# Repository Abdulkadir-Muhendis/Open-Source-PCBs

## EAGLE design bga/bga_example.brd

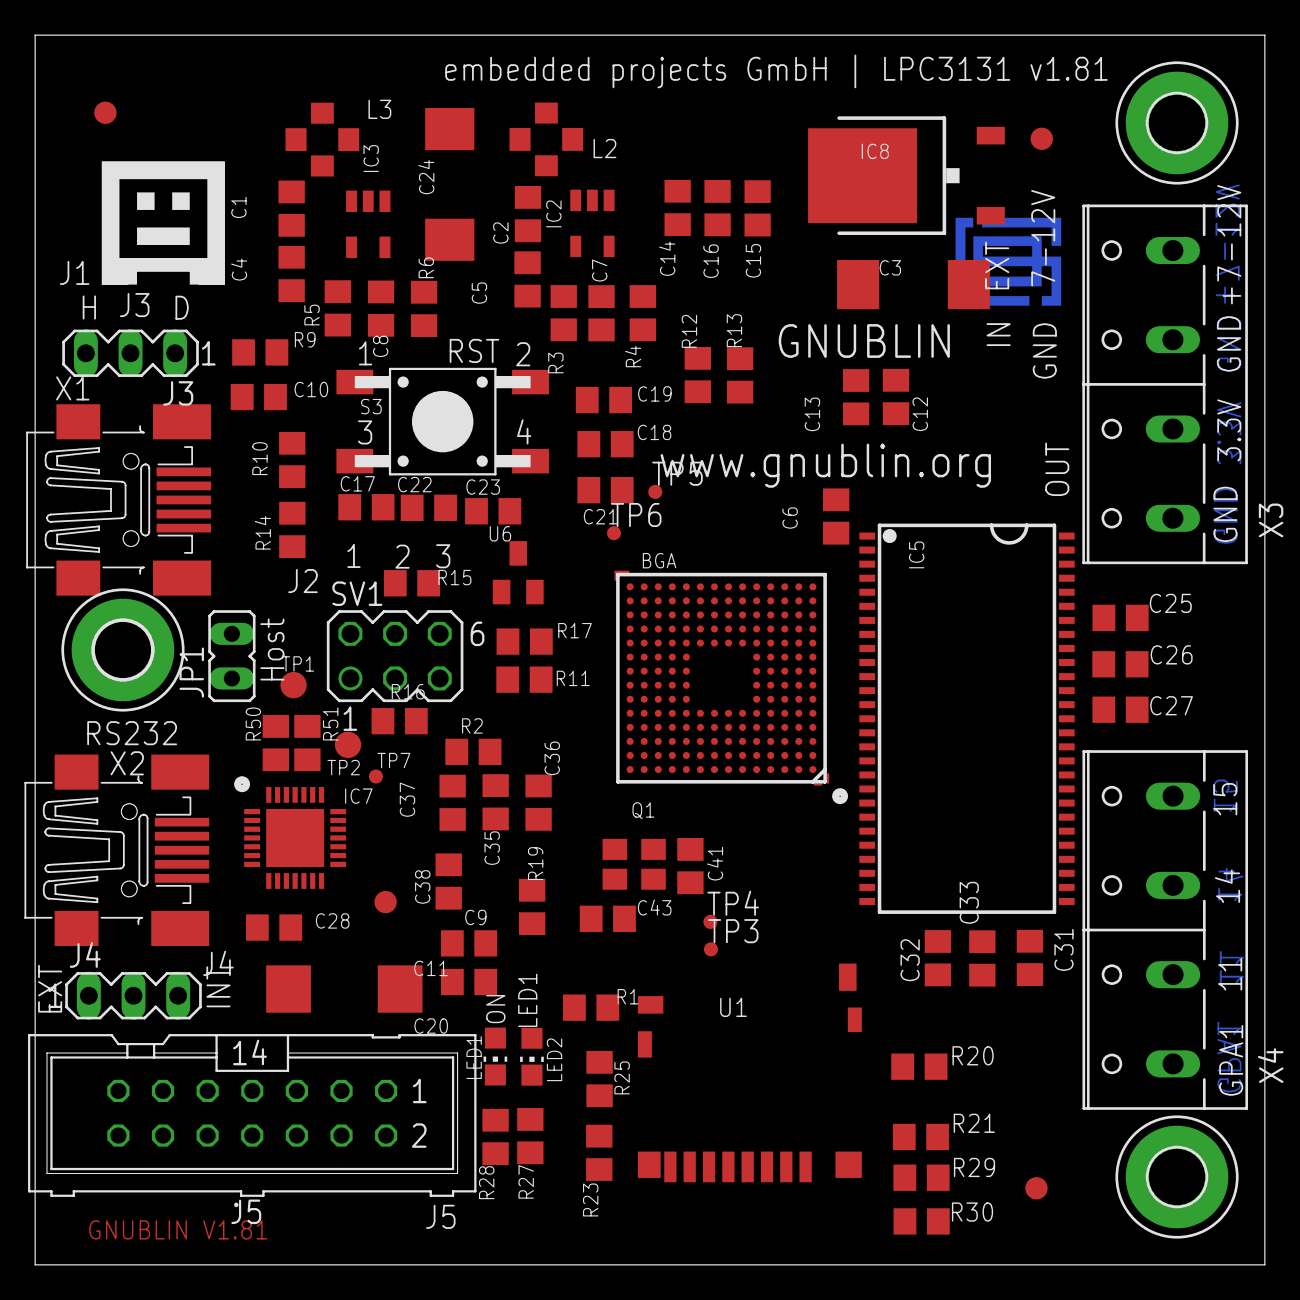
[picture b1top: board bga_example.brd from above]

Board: 4 copper layers, 70.0 x 70.0 mm, 102 parts (1 on the bottom side), 101 nets.

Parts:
BGA: LPC313XFET180; TFBGA180
C1, C2, C11, C13, C14, C21, C23, C27, C32, C37: 10uF; C0805
C3, C24: 10uF; SMC_D
C4, C5: 4.7uF; C0805
C6, C9, C10, C16, C18, C22, C26, C33, C35, C38: 100nF; C0805
C7, C8, C41, C43: 22pF; C0805
C12, C15, C17, C19, C25, C31, C36: 3.3nF; C0805
C20: 10uF; D/7343-31R
C28: 2.2uF; C0805
FID1, FID2, FID3, FID4: PASSERMARKEN_FIDUCIAL
H1, H4: MOUNT-PAD-ROUND3.2; 3,2-PAD
H2: MOUNT-PAD-ROUND3.3; 3,3-PAD
IC2, IC3: AS1324; TSOT23
IC5: A43E26161TSOPII; TSOPII
IC7: CP21021; MLP28
IC8: MC78M05ABDT; DPACK_3
J3, J4: MA03-1
J5: ML14
JP1: JP1
L2, L3: 4u7; PSU3014
LED1: GRUEN; CHIP-LED0805
LED2: ROT; CHIP-LED0805
Q1: SX-32 12.000 MHz; SX-32
R1, R2, R9, R12, R15, R16, R17, R20, R21, R23, R25, R29, R30: 10K; R0805
R3, R4, R5: 301K; R0805
R6: 66K5; R0805
R10, R14: 1M; R0805
R11: 12K 1%; R0805
R13: DNP; R0805
R19: 22R; R0805
R27, R28: 270R; R0805
R50, R51: 0R; R0805
S3: TASTER-9314_SMD
SV1: MA03-2
TP1, TP2: TPTP15R; TP15R
TP3, TP4: PTR1TP08R; TP08R
TP5, TP6, TP7: TPTP08R; TP08R
U1: DM3D-SF
U6: APX803; SOT23
U$3: GNUBLINLOGOSIEB; GNUSIEBDRUCK
U$4: EPLOGO; EPLOGOKUPFER
X1, X2: MINI-USB-32005-201; 32005-201
X3, X4: W237-4P

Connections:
5V: C4.1, C5.1, C20.+, C24.+, C28.1, IC2.1, IC2.4, IC3.1, IC3.4, IC7.7, IC7.8, J3.3, J4.2
+1V2: BGA.A9, BGA.C6, BGA.C9, BGA.C12, BGA.D11, BGA.E10, BGA.H3, BGA.L1, BGA.L7, BGA.L12, C2.2, C7.1, C18.2, C19.2, C21.2, C35.2, C36.2, C37.2, C38.2, L2.2, R3.2
+3V3: BGA.B2, BGA.C13, BGA.D5, BGA.D7, BGA.E5, BGA.E8, BGA.F5, BGA.G5, BGA.G12, BGA.H5, BGA.K11, BGA.L4, BGA.L10, BGA.M2, BGA.M5, BGA.M7, BGA.M9, BGA.P1, C1.2, C6.2, C8.1, C12.2, C13.2, C14.2, C15.2, C16.2, C17.2, C22.2, C23.2, C25.2, C26.2, C27.2, C31.2, C32.2, C33.2, IC5.1, IC5.3, IC5.9, IC5.14, IC5.27, IC5.43, IC5.49, J5.13, L3.2, LED1.A, R1.2, R2.1, R5.2, R12.2, R17.2, R19.1, R20.1, R21.1, R23.1, R25.1, R29.1, R30.1, SV1.5, SV1.6, U1.4, U6.3, X3.2
+5V_USB: J4.3, X2.1
+7-12V: C3.+, IC8.1, X3.4
D+: IC7.4, X2.3
D-: IC7.5, X2.2
EXT_5V: IC8.3, J4.1
GND: BGA.A11, BGA.A12, BGA.B12, BGA.C3, BGA.C4, BGA.C7, BGA.D6, BGA.D8, BGA.D9, BGA.D12, BGA.E4, BGA.E9, BGA.F4, BGA.G4, BGA.G11, BGA.H4, BGA.K3, BGA.K4, BGA.L3, BGA.L6, BGA.L9, BGA.L11, BGA.L13, BGA.M3, BGA.M4, BGA.M6, BGA.M8, BGA.N1, C1.1, C2.1, C3.-, C4.2, C5.2, C6.1, C9.1, C10.1, C11.1, C12.1, C13.1, C14.1, C15.1, C16.1, C17.1, C18.1, C19.1, C20.-, C21.1, C22.1, C23.1, C24.-, C25.1, C26.1, C27.1, C28.2, C31.1, C32.1, C33.1, C35.1, C36.1, C37.1, C38.1, C41.1, C43.1, IC2.2, IC3.2, IC5.6, IC5.12, IC5.28, IC5.41, IC5.46, IC5.52, IC5.54, IC7.3, IC7.EXP, IC8.4, J5.14, JP1.1, R4.1, R6.1, R10.1, R11.1, R13.1, R14.1, R27.1, R28.1, S3.3, S3.4, SV1.1, SV1.2, U1.6, U1.SW_B, U6.1, X1.5, X2.5, X3.1, X3.3
GPA0: BGA.B14, J5.1
GPA1: BGA.A14, J5.2, X4.1
GPA3: BGA.C14, J5.3
GPIO0: BGA.K10, R15.1
GPIO2: BGA.L14, R16.2
GPIO11: BGA.H13, J5.12, X4.2
GPIO14: BGA.J14, J5.11, X4.3
GPIO15: BGA.J13, X4.4
I2C_SCL: BGA.E13, J5.5
I2C_SDA: BGA.E12, J5.6
LED1: BGA.B11, LED2.A
LPC_A0: BGA.B3, IC5.23
LPC_A1: BGA.A2, IC5.24
LPC_A2: BGA.N6, IC5.25
LPC_A3: BGA.P6, IC5.26
LPC_A4: BGA.N7, IC5.29
LPC_A5: BGA.P7, IC5.30
LPC_A6: BGA.K6, IC5.31
LPC_A7: BGA.P5, IC5.32
LPC_A8: BGA.N5, IC5.33
LPC_A9: BGA.L5, IC5.34
LPC_A10: BGA.K7, IC5.22
LPC_A11: BGA.N4, IC5.35
LPC_A12: BGA.K5, IC5.36
LPC_A13: BGA.P4, IC5.21
LPC_A14: BGA.P3, IC5.20
LPC_CAS: BGA.G1, IC5.17
LPC_CKE: BGA.L8, IC5.37
LPC_CLK: BGA.N8, IC5.38
LPC_CS: BGA.P8, IC5.19
LPC_D0: BGA.G2, IC5.2
LPC_D1: BGA.F2, IC5.4
LPC_D2: BGA.F1, IC5.5
LPC_D3: BGA.E1, IC5.7
LPC_D4: BGA.E2, IC5.8
LPC_D5: BGA.D1, IC5.10
LPC_D6: BGA.D2, IC5.11
LPC_D7: BGA.C1, IC5.13
LPC_D8: BGA.B1, IC5.42
LPC_D9: BGA.A3, IC5.44
LPC_D10: BGA.A1, IC5.45
LPC_D11: BGA.C2, IC5.47
LPC_D12: BGA.G3, IC5.48
LPC_D13: BGA.D3, IC5.50
LPC_D14: BGA.E3, IC5.51
LPC_D15: BGA.F3, IC5.53
LPC_DM: BGA.N2, R10.2, X1.2
LPC_DP: BGA.P2, R14.2, X1.3
LPC_DQM0: BGA.H1, IC5.15
LPC_DQM1: BGA.N9, IC5.39
LPC_MCI_CD: BGA.B4, R20.2, U1.SW_A
LPC_MCI_CLK: BGA.B6, U1.5
LPC_MCI_CMD: BGA.A6, R29.2, U1.3
LPC_MCI_DAT0: BGA.A5, R25.2, U1.7
LPC_MCI_DAT1: BGA.B5, R23.2, U1.8
LPC_MCI_DAT2: BGA.C5, R30.2, U1.1
LPC_MCI_DAT3: BGA.A4, R21.2, U1.2
LPC_RAS: BGA.H2, IC5.18
LPC_RXD: BGA.P12, R50.2, TP1.TP
LPC_TXD: BGA.N12, R51.2, TP2.TP
LPC_VBUS: C10.2, J3.1, R9.1
LPC_WE: BGA.J2, IC5.16
unnamed: IC7.26, R50.1
unnamed: IC7.25, R51.1
unnamed: LED2.C, R27.2
unnamed: LED1.C, R28.2
unnamed: IC2.3, L2.1
unnamed: BGA.N11, R12.1, R13.2
unnamed: J3.2, X1.1
unnamed: BGA.A7, R1.1, TP3.TP
unnamed: BGA.B8, TP4.TP
unnamed: IC7.24, TP7.TP
unnamed: BGA.J10, R2.2
unnamed: R15.2, SV1.4
unnamed: R16.1, SV1.3
unnamed: BGA.N13, TP5.TP
unnamed: BGA.P14, TP6.TP
unnamed: C7.2, IC2.5, R3.1, R4.2
unnamed: BGA.A13, C9.2, C11.2, R19.2
unnamed: BGA.J5, R11.2
unnamed: BGA.L2, R9.2
unnamed: IC3.3, L3.1
unnamed: C8.2, IC3.5, R5.1, R6.2
PWM_DATA: BGA.B9, J5.4
RESET: BGA.H14, R17.1, S3.2, U6.2
SPI_MISO: BGA.C8, J5.8
SPI_MOSI: BGA.B7, J5.7
SPI_SCK: BGA.A8, J5.10
SYSCLOCK_O: BGA.G13, J5.9
USB_ID: BGA.M1, JP1.2, X1.4
XTAL1: BGA.A10, C43.2, Q1.3
XTAL2: BGA.B10, C41.2, Q1.1

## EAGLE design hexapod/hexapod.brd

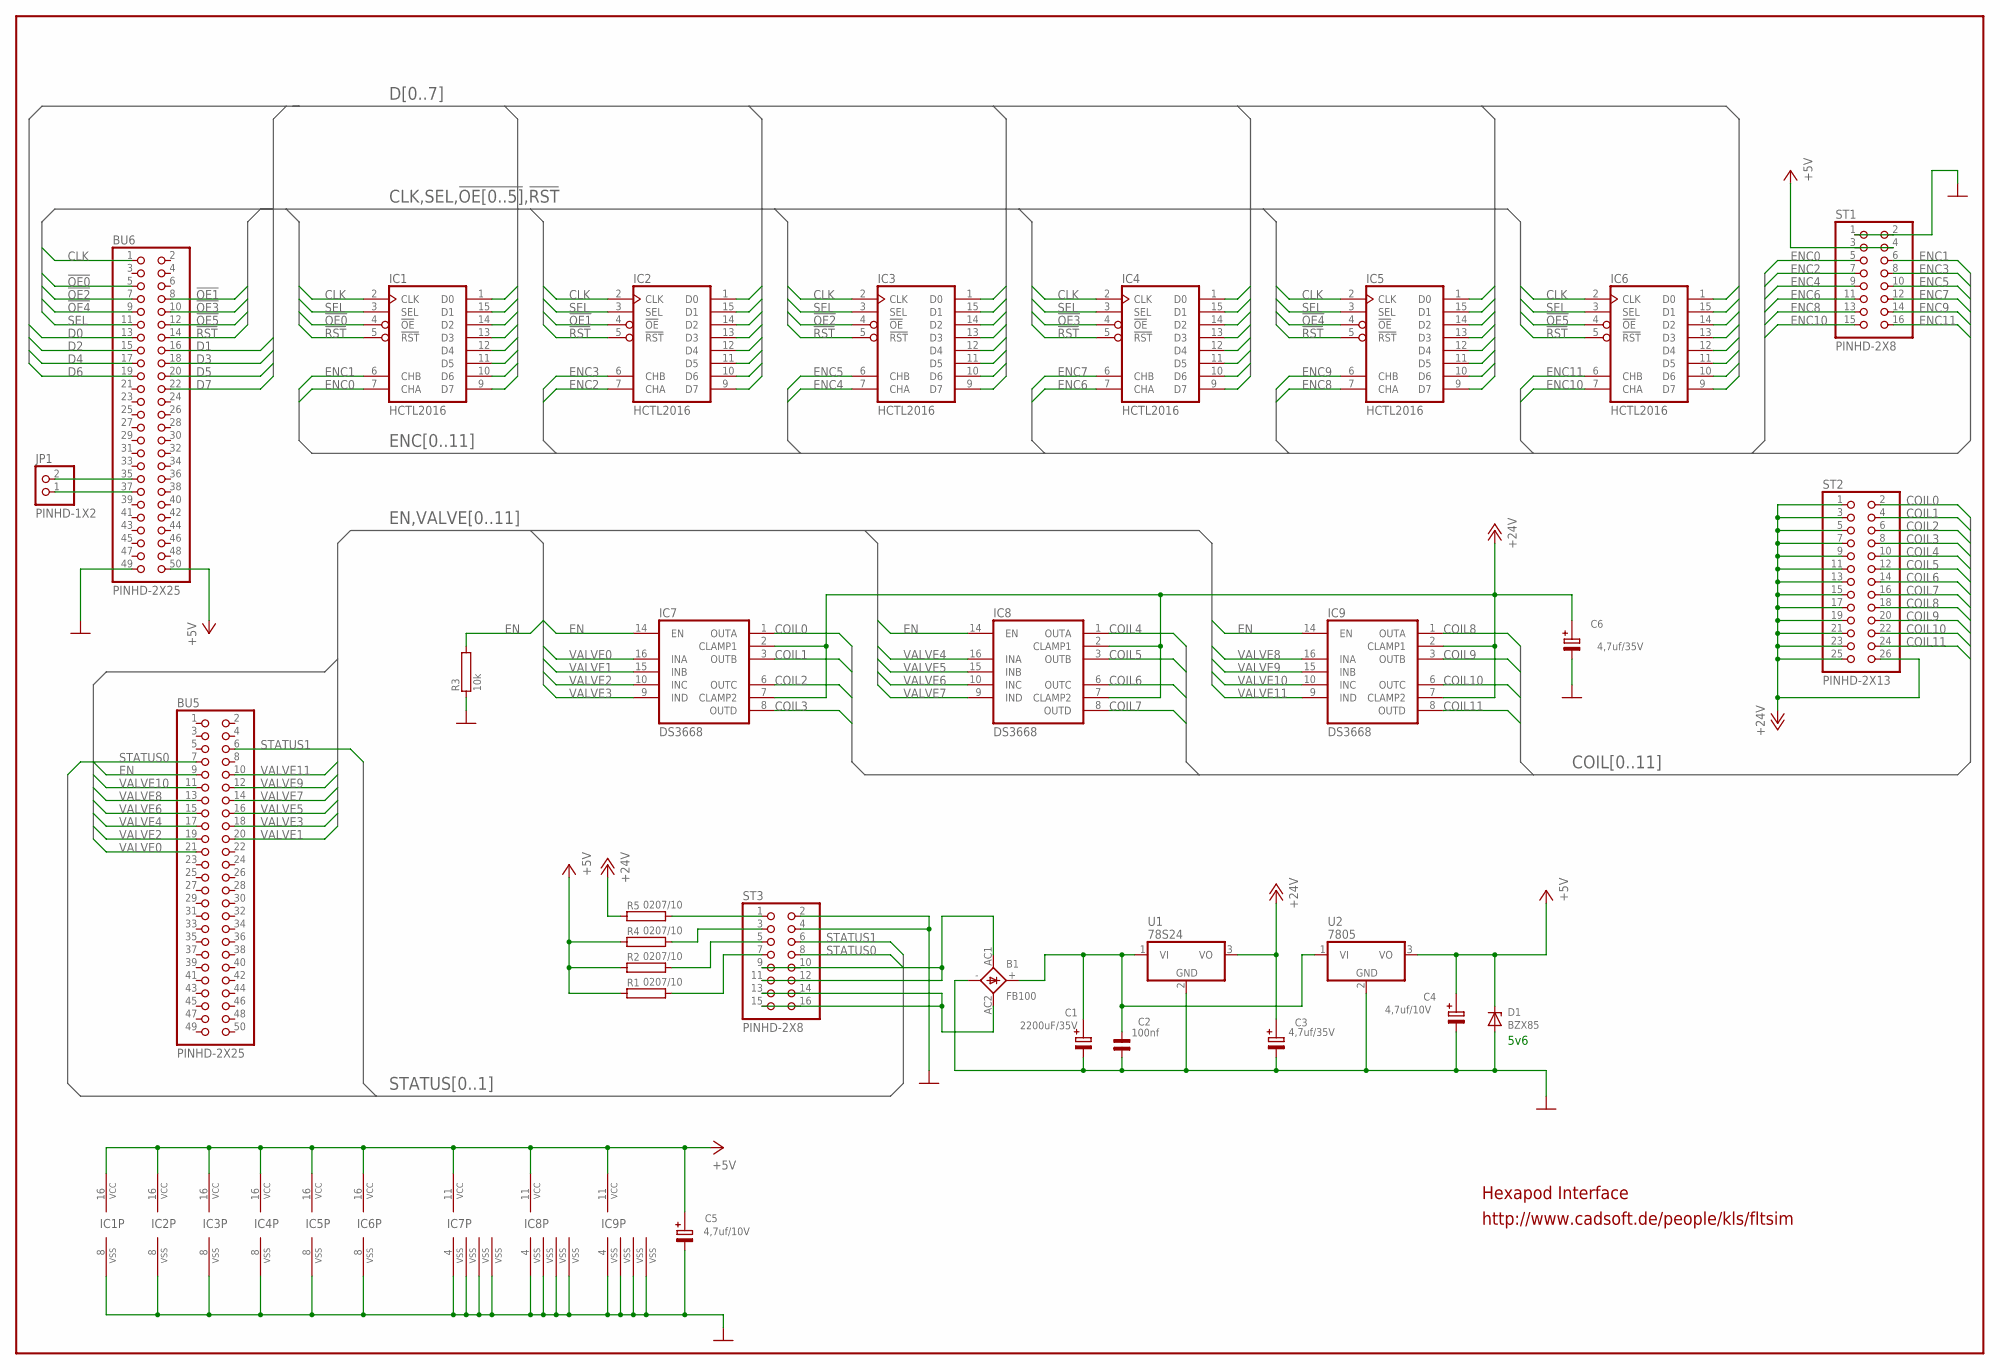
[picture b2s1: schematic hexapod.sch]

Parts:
B1: FB100
BU5, BU6: PINHD-2X25; 2X25
C1: 2200uF/35V; E35-16
C2: 100nf; C5B2,5A
C3, C6: 4,7uf/35V; E2,5-5
C4, C5: 4,7uf/10V; E2,5-5
D1: BZX85; DO41Z10
IC1, IC2, IC3, IC4, IC5, IC6: HCTL2016; DIL-16
IC7, IC8, IC9: DS3668; DIL-16
JP1: PINHD-1X2; 1X02
R1, R2, R4, R5: 0207/10
R3: 10k; 0207/10@1
ST1, ST3: PINHD-2X8; ML16
ST2: PINHD-2X13; ML26
U1: 78S24; TO220H
U2: 7805; TO220H

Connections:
!OE0: BU6.5, IC1.4 (!OE)
!OE1: BU6.8, IC2.4 (!OE)
!OE2: BU6.7, IC3.4 (!OE)
!OE3: BU6.10, IC4.4 (!OE)
!OE4: BU6.9, IC5.4 (!OE)
!OE5: BU6.12, IC6.4 (!OE)
!RST: BU6.14, IC1.5 (!RST), IC2.5 (!RST), IC3.5 (!RST), IC4.5 (!RST), IC5.5 (!RST), IC6.5 (!RST)
+5V: BU6.50, C4.+, C5.+, D1.K, IC1.16 (VCC), IC2.16 (VCC), IC3.16 (VCC), IC4.16 (VCC), IC5.16 (VCC), IC6.16 (VCC), IC7.11 (VCC), IC8.11 (VCC), IC9.11 (VCC), R1.1, R2.1, R4.1, ST1.3, ST1.4, U2.3 (VO)
+24V: C3.+, C6.+, IC7.2 (CLAMP1), IC7.7 (CLAMP2), IC8.2 (CLAMP1), IC8.7 (CLAMP2), IC9.2 (CLAMP1), IC9.7 (CLAMP2), R5.1, ST2.1, ST2.3, ST2.5, ST2.7, ST2.9, ST2.11, ST2.13, ST2.15, ST2.17, ST2.19, ST2.21, ST2.23, ST2.25, ST2.26, U1.3 (VO)
AC1: B1.AC1, ST3.9, ST3.10, ST3.11, ST3.12
AC2: B1.AC2, ST3.13, ST3.14, ST3.15, ST3.16
CLK: BU6.1, IC1.2 (CLK), IC2.2 (CLK), IC3.2 (CLK), IC4.2 (CLK), IC5.2 (CLK), IC6.2 (CLK)
COIL0: IC7.1 (OUTA), ST2.2
COIL1: IC7.3 (OUTB), ST2.4
COIL2: IC7.6 (OUTC), ST2.6
COIL3: IC7.8 (OUTD), ST2.8
COIL4: IC8.1 (OUTA), ST2.10
COIL5: IC8.3 (OUTB), ST2.12
COIL6: IC8.6 (OUTC), ST2.14
COIL7: IC8.8 (OUTD), ST2.16
COIL8: IC9.1 (OUTA), ST2.18
COIL9: IC9.3 (OUTB), ST2.20
COIL10: IC9.6 (OUTC), ST2.22
COIL11: IC9.8 (OUTD), ST2.24
D0: BU6.13, IC1.1 (D0), IC2.1 (D0), IC3.1 (D0), IC4.1 (D0), IC5.1 (D0), IC6.1 (D0)
D1: BU6.16, IC1.15 (D1), IC2.15 (D1), IC3.15 (D1), IC4.15 (D1), IC5.15 (D1), IC6.15 (D1)
D2: BU6.15, IC1.14 (D2), IC2.14 (D2), IC3.14 (D2), IC4.14 (D2), IC5.14 (D2), IC6.14 (D2)
D3: BU6.18, IC1.13 (D3), IC2.13 (D3), IC3.13 (D3), IC4.13 (D3), IC5.13 (D3), IC6.13 (D3)
D4: BU6.17, IC1.12 (D4), IC2.12 (D4), IC3.12 (D4), IC4.12 (D4), IC5.12 (D4), IC6.12 (D4)
D5: BU6.20, IC1.11 (D5), IC2.11 (D5), IC3.11 (D5), IC4.11 (D5), IC5.11 (D5), IC6.11 (D5)
D6: BU6.19, IC1.10 (D6), IC2.10 (D6), IC3.10 (D6), IC4.10 (D6), IC5.10 (D6), IC6.10 (D6)
D7: BU6.22, IC1.9 (D7), IC2.9 (D7), IC3.9 (D7), IC4.9 (D7), IC5.9 (D7), IC6.9 (D7)
EN: BU5.9, IC7.14 (EN), IC8.14 (EN), IC9.14 (EN), R3.2
ENC0: IC1.7 (CHA), ST1.5
ENC1: IC1.6 (CHB), ST1.6
ENC2: IC2.7 (CHA), ST1.7
ENC3: IC2.6 (CHB), ST1.8
ENC4: IC3.7 (CHA), ST1.9
ENC5: IC3.6 (CHB), ST1.10
ENC6: IC4.7 (CHA), ST1.11
ENC7: IC4.6 (CHB), ST1.12
ENC8: IC5.7 (CHA), ST1.13
ENC9: IC5.6 (CHB), ST1.14
ENC10: IC6.7 (CHA), ST1.15
ENC11: IC6.6 (CHB), ST1.16
GND: B1.-, BU6.49, C1.-, C2.1, C3.-, C4.-, C5.-, C6.-, D1.A, IC1.8 (VSS), IC2.8 (VSS), IC3.8 (VSS), IC4.8 (VSS), IC5.8 (VSS), IC6.8 (VSS), IC7.4 (VSS), IC7.5 (VSS), IC7.12 (VSS), IC7.13 (VSS), IC8.4 (VSS), IC8.5 (VSS), IC8.12 (VSS), IC8.13 (VSS), IC9.4 (VSS), IC9.5 (VSS), IC9.12 (VSS), IC9.13 (VSS), R3.1, ST1.1, ST1.2, ST3.2, ST3.4, U1.2 (GND), U2.2 (GND)
unnamed: R5.2, ST3.1
unnamed: R4.2, ST3.3
unnamed: R2.2, ST3.5
unnamed: R1.2, ST3.7
unnamed: BU6.35, JP1.2
unnamed: BU6.37, JP1.1
SEL: BU6.11, IC1.3 (SEL), IC2.3 (SEL), IC3.3 (SEL), IC4.3 (SEL), IC5.3 (SEL), IC6.3 (SEL)
STATUS0: BU5.7, ST3.8
STATUS1: BU5.6, ST3.6
VALVE0: BU5.21, IC7.16 (INA)
VALVE1: BU5.20, IC7.15 (INB)
VALVE2: BU5.19, IC7.10 (INC)
VALVE3: BU5.18, IC7.9 (IND)
VALVE4: BU5.17, IC8.16 (INA)
VALVE5: BU5.16, IC8.15 (INB)
VALVE6: BU5.15, IC8.10 (INC)
VALVE7: BU5.14, IC8.9 (IND)
VALVE8: BU5.13, IC9.16 (INA)
VALVE9: BU5.12, IC9.15 (INB)
VALVE10: BU5.11, IC9.10 (INC)
VALVE11: BU5.10, IC9.9 (IND)
VIN: B1.+, C1.+, C2.2, U1.1 (VI), U2.1 (VI)

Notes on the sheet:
Hexapod Interface
5v6
http://www.cadsoft.de/people/kls/fltsim

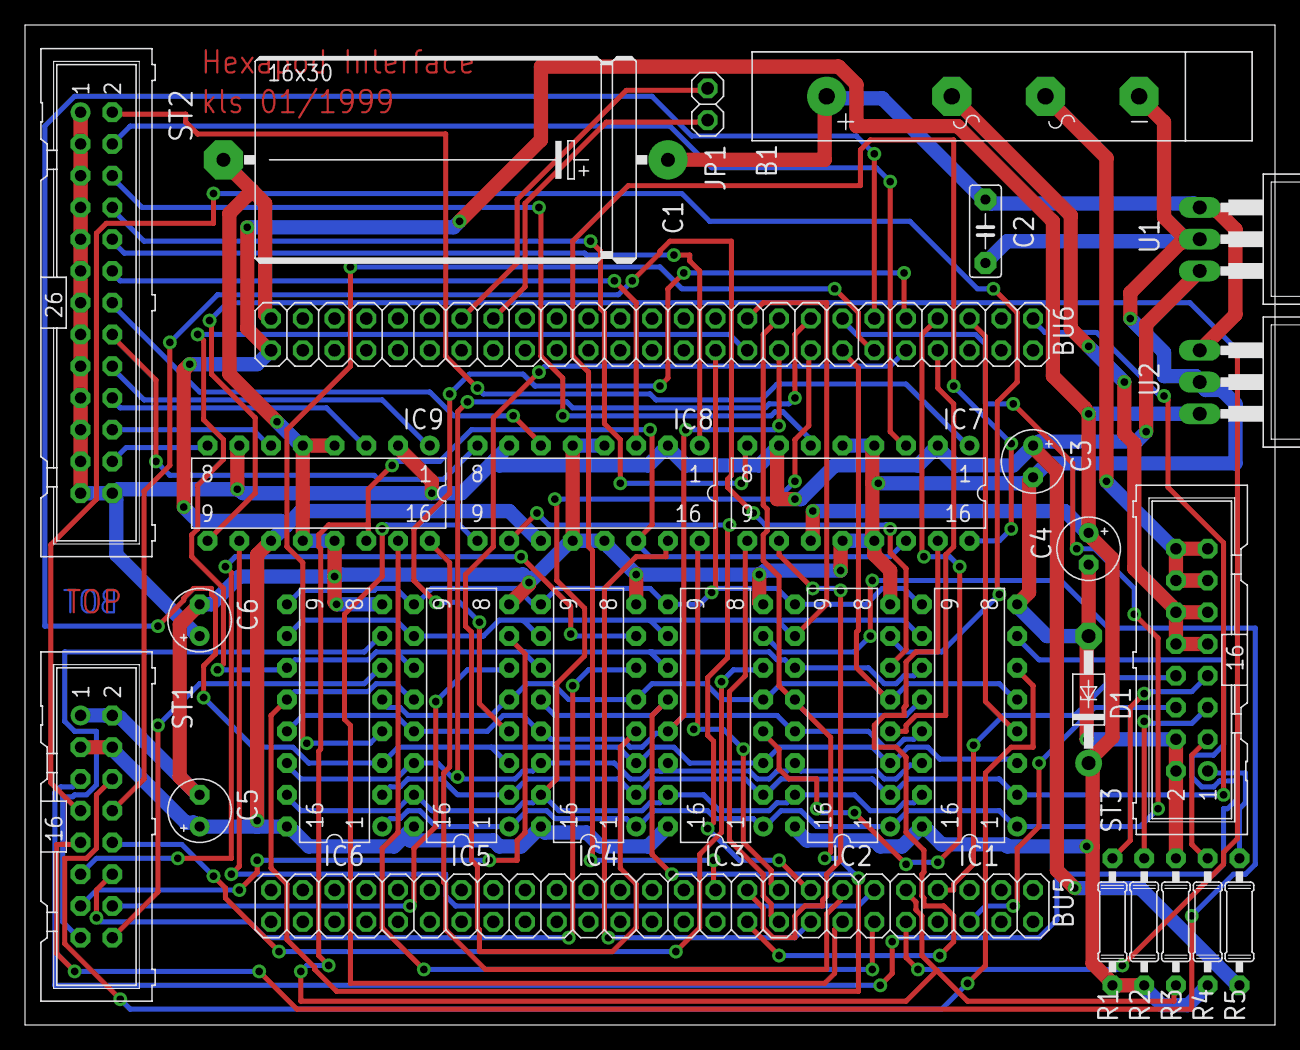
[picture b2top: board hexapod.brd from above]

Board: 2 copper layers, 100.0 x 80.0 mm, 30 parts (0 on the bottom side), 68 nets.

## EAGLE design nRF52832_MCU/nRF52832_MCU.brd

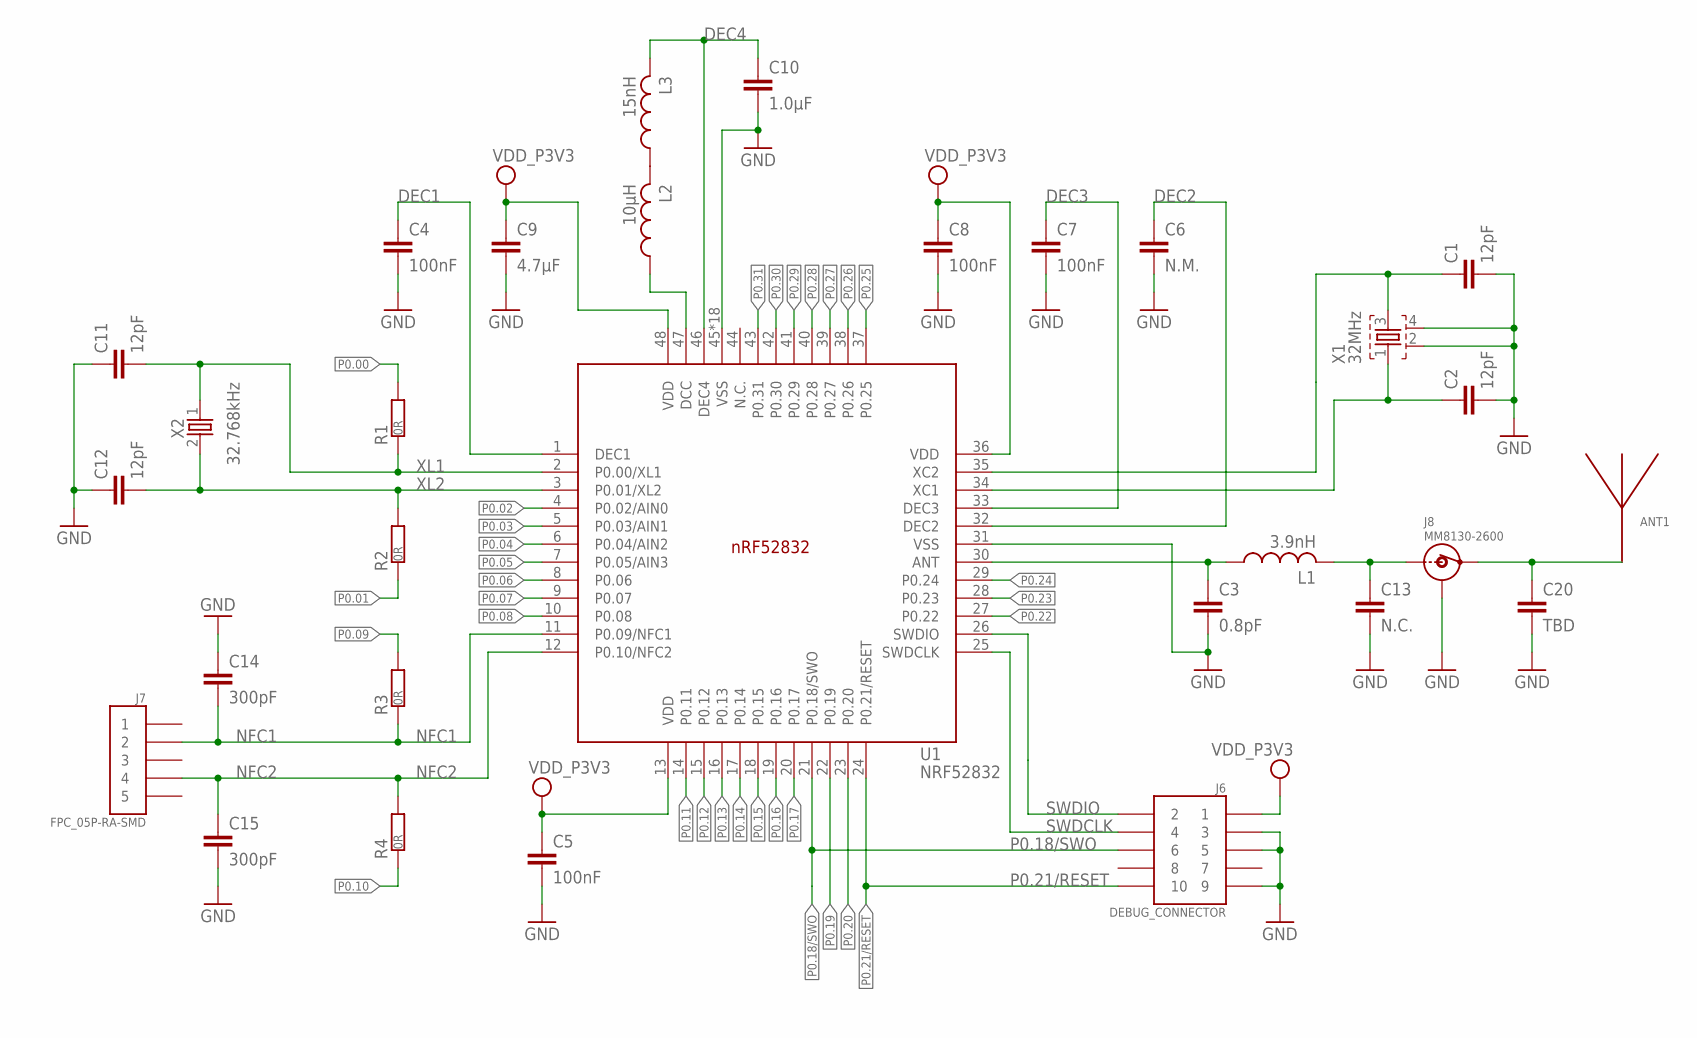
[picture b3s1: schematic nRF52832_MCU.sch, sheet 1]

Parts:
ANT1: ANTENNA_QUARTER-WAVE_MONOPOLE_MEANDERED_LEFT; QWMP_MEANDERED_LEFT_+6
C1, C2, C11, C12: 12pF; RESC0402_N
C3: 0.8pF; RESC0402_N
C4, C5, C7, C8: 100nF; RESC0402_N
C6: N.M.; RESC0402_N
C9: 4.7µF; RESC0603_N
C10: 1.0µF; RESC0603_N
C13: N.C.; RESC0402_N
C14, C15: 300pF; RESC0402_N
C20: TBD; RESC0402_N
J6: DEBUG_CONNECTOR; HDRV127P5X2-10_N
J7: FPC_05P-RA-SMD
J8: MM8130-2600
L1: 3.9nH; RESC0402_N
L2: 10µH; RESC0603_N
L3: 15nH; RESC0402_N
R1, R2, R3, R4: 0R; RESC0402_N
U1: NRF52832; QFN40P600X600X90-48_N
X1: 32MHz; BT-XTAL_2016_N
X2: 32.768kHz; XTAL_3215_N

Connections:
ANT: C3.1, L1.1, U1.30 (ANT)
DEC1: C4.1, U1.1 (DEC1)
DEC2: C6.1, U1.32 (DEC2)
DEC3: C7.1, U1.33 (DEC3)
DEC4: C10.1, L3.2, U1.46 (DEC4)
GND: C1.2, C2.2, C3.2, C4.2, C5.2, C6.2, C7.2, C8.2, C9.2, C10.2, C11.1, C12.1, C13.2, C14.1, C15.2, C20.2, J6.3, J6.5, J6.9, J8.1, J8.2, J8.3, J8.4, U1.31 (VSS), U1.45 (VSS), U1.PAD (VSS), U1.PAD@VIA01 (VSS), U1.PAD@VIA02 (VSS), U1.PAD@VIA03 (VSS), U1.PAD@VIA04 (VSS), U1.PAD@VIA05 (VSS), U1.PAD@VIA06 (VSS), U1.PAD@VIA07 (VSS), U1.PAD@VIA08 (VSS), U1.PAD@VIA09 (VSS), U1.PAD@VIA10 (VSS), U1.PAD@VIA11 (VSS), U1.PAD@VIA12 (VSS), U1.PAD@VIA13 (VSS), U1.PAD@VIA14 (VSS), U1.PAD@VIA15 (VSS), U1.PAD@VIA16 (VSS), X1.2, X1.4; also elsewhere on the board
unnamed: ANT1.P$1, C20.1, J8.OUT
unnamed: L2.2, L3.1
unnamed: C1.1, U1.35 (XC2), X1.3
unnamed: L2.1, U1.47 (DCC)
unnamed: C13.1, J8.IN, L1.2
NFC1: C14.2, J7.2, R3.1, U1.11 (P0.09/NFC1)
NFC2: C15.1, J7.4, R4.2, U1.12 (P0.10/NFC2)
P0.00: R1.2; also elsewhere on the board
P0.01: R2.1; also elsewhere on the board
P0.02: U1.4 (P0.02/AIN0); also elsewhere on the board
P0.03: U1.5 (P0.03/AIN1); also elsewhere on the board
P0.04: U1.6 (P0.04/AIN2); also elsewhere on the board
P0.05: U1.7 (P0.05/AIN3); also elsewhere on the board
P0.06: U1.8 (P0.06); also elsewhere on the board
P0.07: U1.9 (P0.07); also elsewhere on the board
P0.08: U1.10 (P0.08); also elsewhere on the board
P0.09: R3.2; also elsewhere on the board
P0.10: R4.1; also elsewhere on the board
P0.11: U1.14 (P0.11); also elsewhere on the board
P0.12: U1.15 (P0.12); also elsewhere on the board
P0.13: U1.16 (P0.13); also elsewhere on the board
P0.14: U1.17 (P0.14); also elsewhere on the board
P0.15: U1.18 (P0.15); also elsewhere on the board
P0.16: U1.19 (P0.16); also elsewhere on the board
P0.17: U1.20 (P0.17); also elsewhere on the board
P0.18/SWO: J6.6, U1.21 (P0.18/SWO); also elsewhere on the board
P0.19: U1.22 (P0.19); also elsewhere on the board
P0.20: U1.23 (P0.20); also elsewhere on the board
P0.21/RESET: J6.10, U1.24 (P0.21/RESET); also elsewhere on the board
P0.22: U1.27 (P0.22); also elsewhere on the board
P0.23: U1.28 (P0.23); also elsewhere on the board
P0.24: U1.29 (P0.24); also elsewhere on the board
P0.25: U1.37 (P0.25); also elsewhere on the board
P0.26: U1.38 (P0.26); also elsewhere on the board
P0.27: U1.39 (P0.27); also elsewhere on the board
P0.28: U1.40 (P0.28); also elsewhere on the board
P0.29: U1.41 (P0.29); also elsewhere on the board
P0.30: U1.42 (P0.30); also elsewhere on the board
P0.31: U1.43 (P0.31); also elsewhere on the board
SWDCLK: J6.4, U1.25 (SWDCLK)
SWDIO: J6.2, U1.26 (SWDIO)
VDD_P3V3: C5.1, C8.1, C9.1, J6.1, U1.13 (VDD), U1.36 (VDD), U1.48 (VDD); also elsewhere on the board
X1: C2.1, U1.34 (XC1), X1.1
XL1: C11.2, R1.1, U1.2 (P0.00/XL1), X2.1
XL2: C12.2, R2.2, U1.3 (P0.01/XL2), X2.2

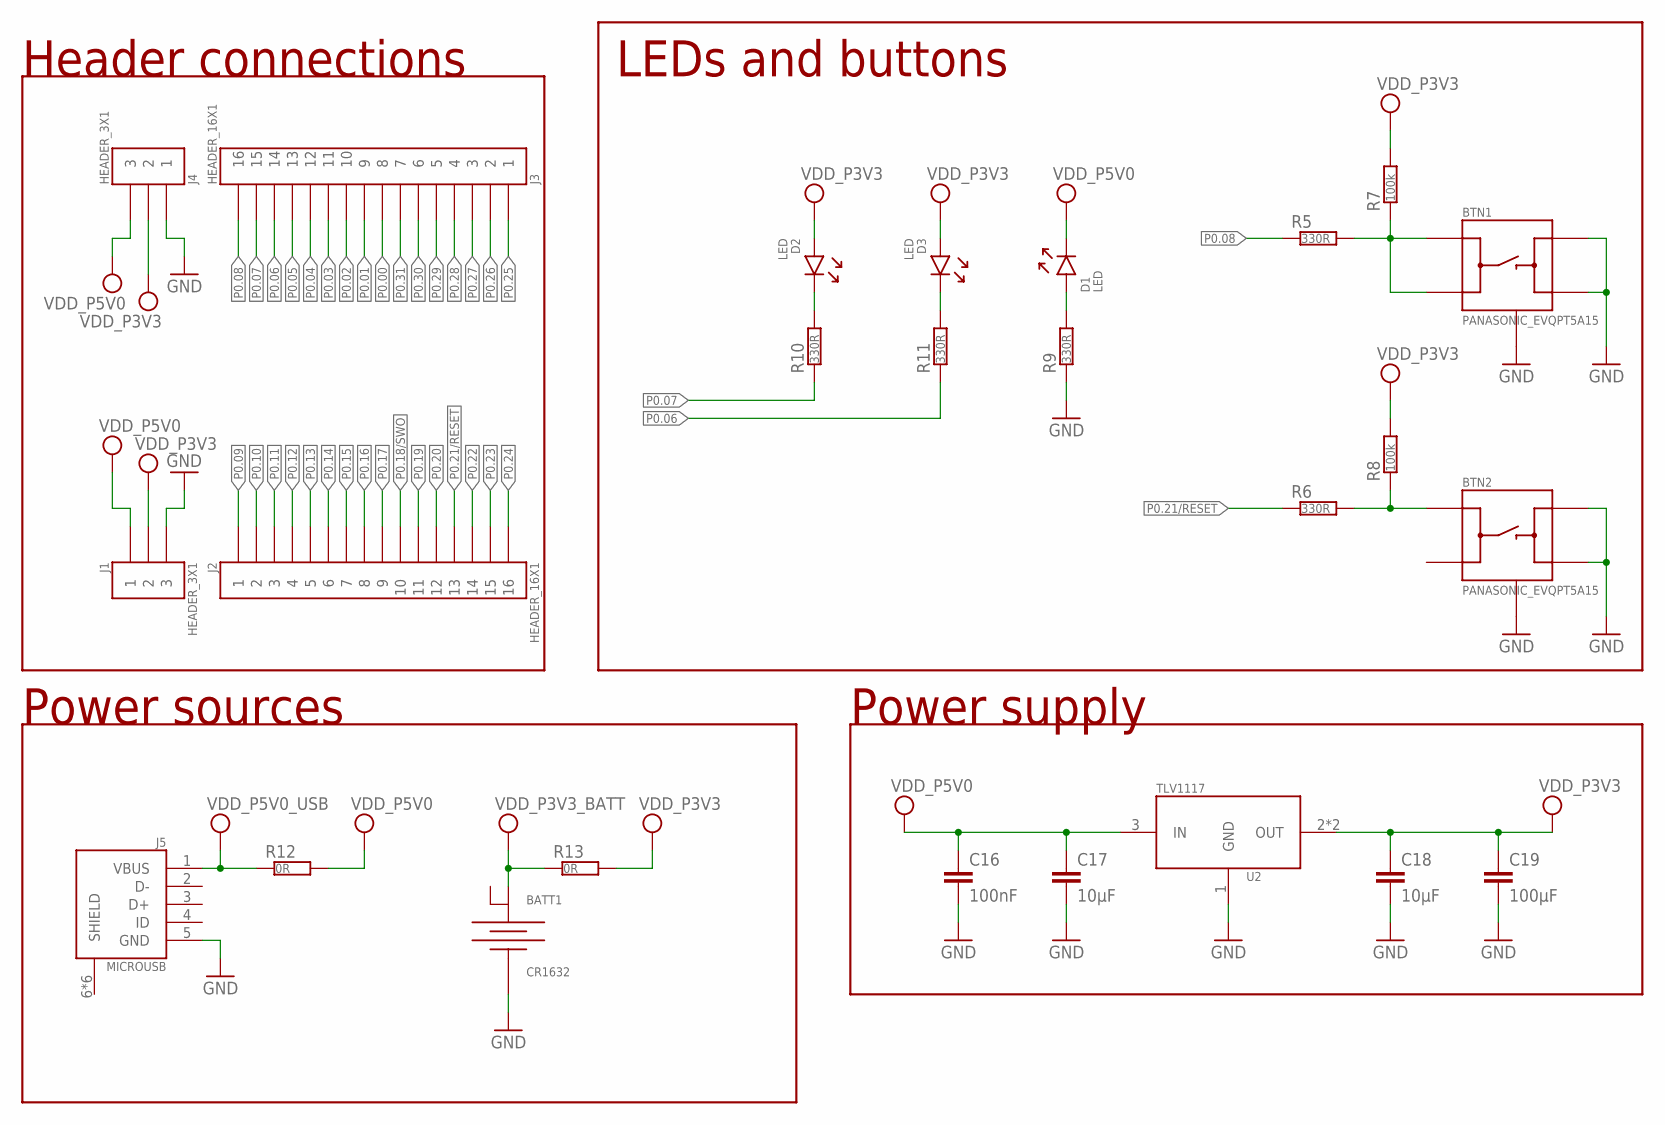
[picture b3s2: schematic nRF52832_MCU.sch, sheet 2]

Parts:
BATT1: CR1632; CR1632_HOLDER_TH
BTN1, BTN2: PANASONIC_EVQPT5A15
C16: 100nF; RESC0402_N
C17, C18: 10µF; RESC0603_N
C19: 100µF; RESC0805_N
D1, D2, D3: LED; DIOC0603_N
J1, J4: HEADER_3X1; HDRV3W64P254_1X3_762X254X900B_NO_SILK
J2, J3: HEADER_16X1; HDRV16W64P254_1X16_4064X254X900B_NO_SILK
J5: MICROUSB; USB-MICRO-B-RA-SMD-PIP
R5, R6, R9, R10, R11: 330R; RESC0402_N
R7, R8: 100k; RESC0402_N
R12, R13: 0R; RESC0402_N
U2: TLV1117; SOT220P700-4_N

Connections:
GND: BATT1.1 (-), BTN1.3 (B), BTN1.4 (B'), BTN1.5 (GND), BTN1.6 (GND), BTN2.3 (B), BTN2.4 (B'), BTN2.5 (GND), BTN2.6 (GND), C16.2, C17.2, C18.2, C19.2, J1.P$3 (3), J4.P$1 (1), J5.5 (GND), R9.1, U2.1 (GND); also elsewhere on the board
unnamed: BTN2.1 (A), R6.2, R8.1
unnamed: BTN1.1 (A), BTN1.2 (A'), R5.2, R7.1
unnamed: D2.1 (C), R10.2
unnamed: D3.1 (C), R11.2
P0.00: J3.P$8 (8); also elsewhere on the board
P0.01: J3.P$9 (9); also elsewhere on the board
P0.02: J3.P$10 (10); also elsewhere on the board
P0.03: J3.P$11 (11); also elsewhere on the board
P0.04: J3.P$12 (12); also elsewhere on the board
P0.05: J3.P$13 (13); also elsewhere on the board
P0.06: J3.P$14 (14), R11.1; also elsewhere on the board
P0.07: J3.P$15 (15), R10.1; also elsewhere on the board
P0.08: J3.P$16 (16), R5.1; also elsewhere on the board
P0.09: J2.P$1 (1); also elsewhere on the board
P0.10: J2.P$2 (2); also elsewhere on the board
P0.11: J2.P$3 (3); also elsewhere on the board
P0.12: J2.P$4 (4); also elsewhere on the board
P0.13: J2.P$5 (5); also elsewhere on the board
P0.14: J2.P$6 (6); also elsewhere on the board
P0.15: J2.P$7 (7); also elsewhere on the board
P0.16: J2.P$8 (8); also elsewhere on the board
P0.17: J2.P$9 (9); also elsewhere on the board
P0.18/SWO: J2.P$10 (10); also elsewhere on the board
P0.19: J2.P$11 (11); also elsewhere on the board
P0.20: J2.P$12 (12); also elsewhere on the board
P0.21/RESET: J2.P$13 (13), R6.1; also elsewhere on the board
P0.22: J2.P$14 (14); also elsewhere on the board
P0.23: J2.P$15 (15); also elsewhere on the board
P0.24: J2.P$16 (16); also elsewhere on the board
P0.25: J3.P$1 (1); also elsewhere on the board
P0.26: J3.P$2 (2); also elsewhere on the board
P0.27: J3.P$3 (3); also elsewhere on the board
P0.28: J3.P$4 (4); also elsewhere on the board
P0.29: J3.P$5 (5); also elsewhere on the board
P0.30: J3.P$6 (6); also elsewhere on the board
P0.31: J3.P$7 (7); also elsewhere on the board
VCC_P5V0_USB: J5.1 (VBUS), R12.1
VDD_LED: D1.2 (A), R9.2
VDD_P3V3: C18.1, C19.1, D2.2 (A), D3.2 (A), J1.P$2 (2), J4.P$2 (2), R7.2, R8.2, R13.2, U2.2 (OUT), U2.4 (OUT); also elsewhere on the board
VDD_P3V3_BATT: BATT1.2 (+), R13.1
VDD_P5V0: C16.1, C17.1, D1.1 (C), J1.P$1 (1), J4.P$3 (3), R12.2, U2.3 (IN)

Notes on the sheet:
Power supply
Power sources
Header connections
LEDs and buttons

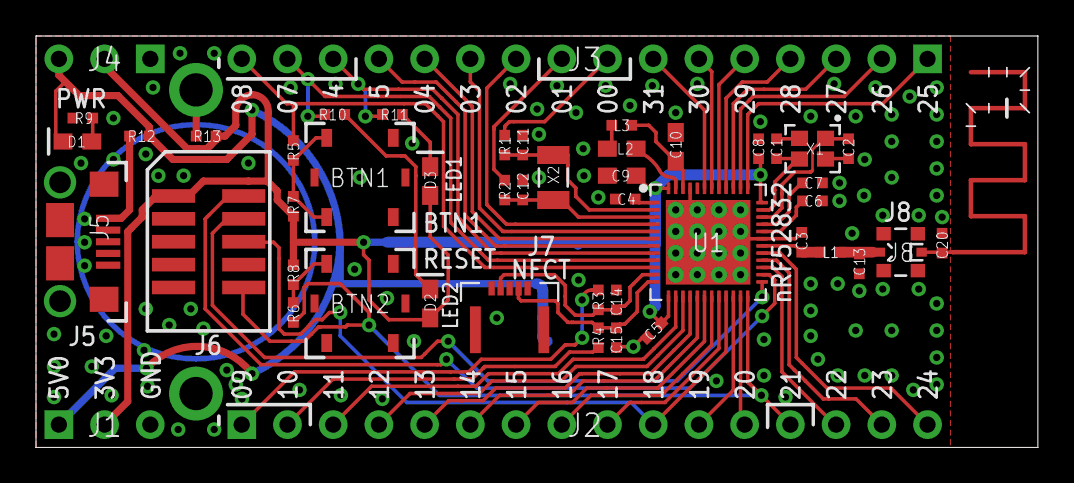
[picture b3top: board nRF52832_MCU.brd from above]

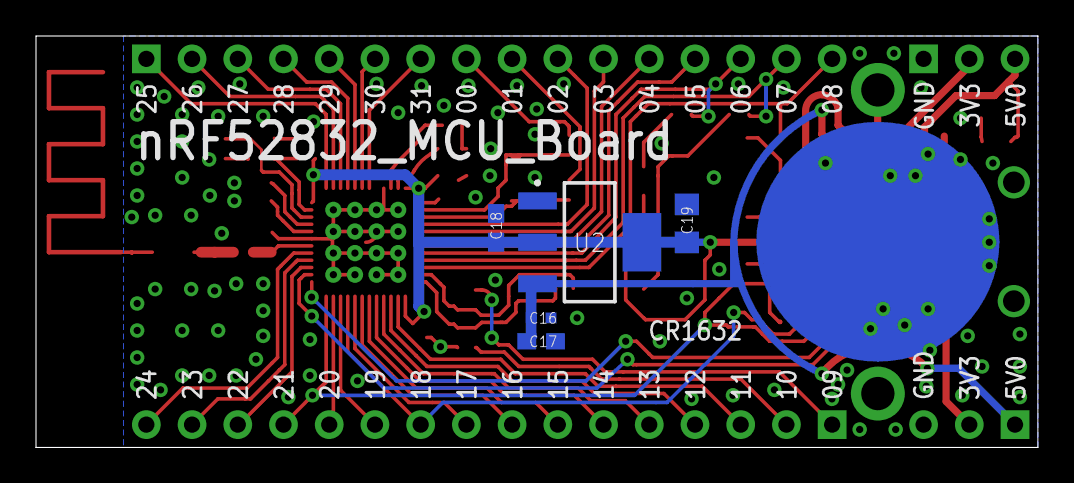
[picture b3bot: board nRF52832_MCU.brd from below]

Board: 2 copper layers, 55.7 x 22.9 mm, 55 parts (6 on the bottom side), 59 nets.
